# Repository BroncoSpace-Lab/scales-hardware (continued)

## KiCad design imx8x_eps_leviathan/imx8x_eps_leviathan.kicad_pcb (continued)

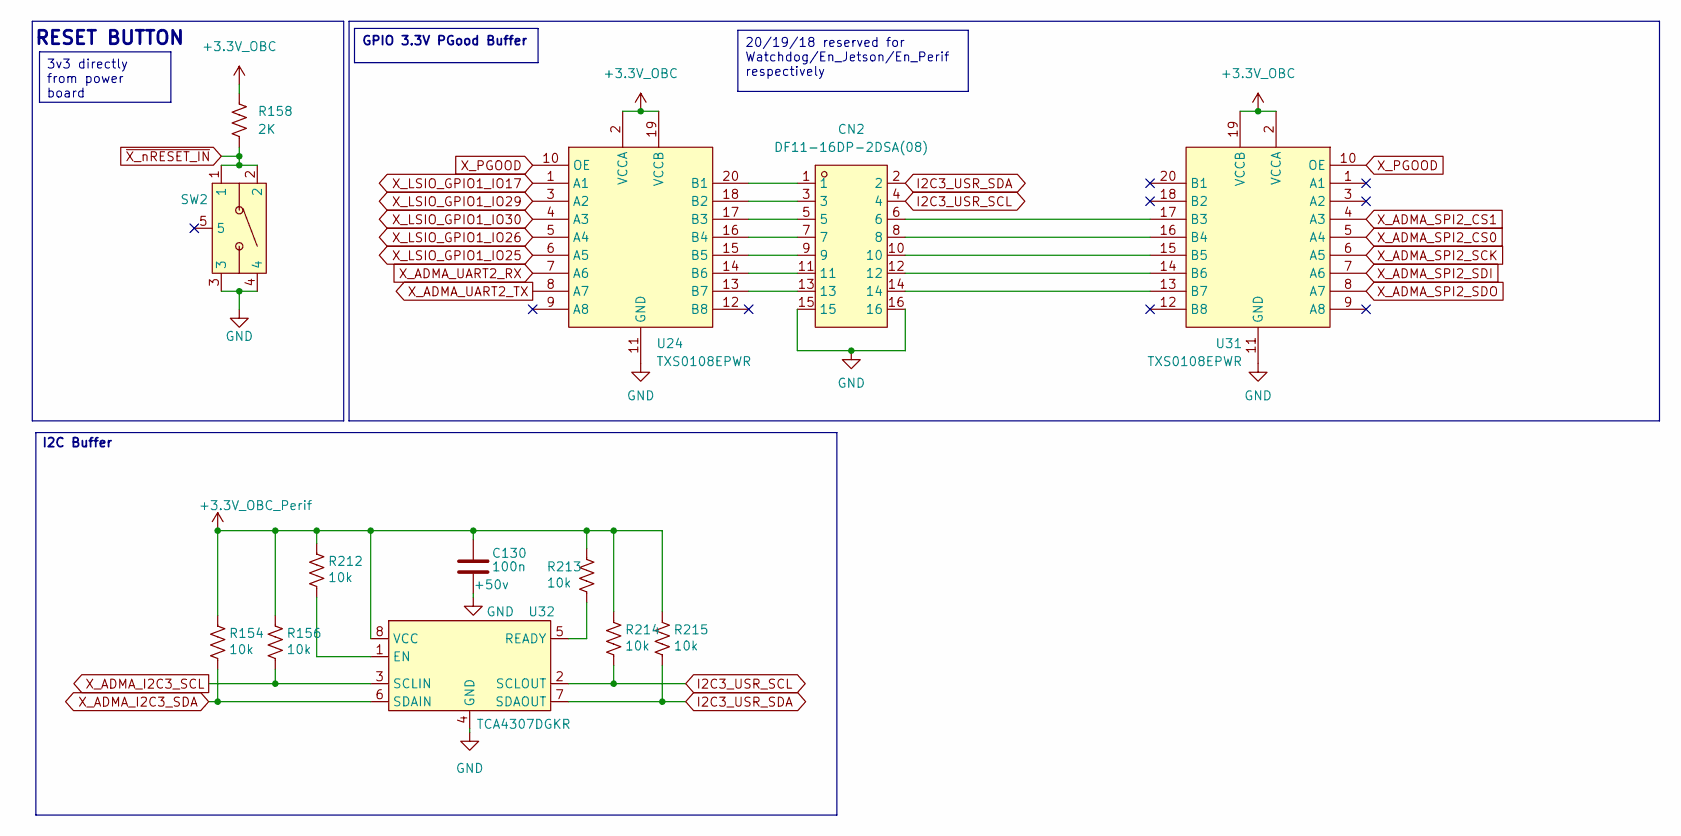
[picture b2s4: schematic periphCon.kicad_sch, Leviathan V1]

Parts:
C130: 100n; C0402; Voltage Rating +50v; LCSC C85858
CN2: DF11-16DP-2DSA(08); CONN-TH_DF11-16DP-2DSA-08; LCSC Part C530981
R154, R156, R212, R213, R214, R215: 10k; R_0603_1608Metric; LCSC C99782
R158: 2K; R0402
SW2: KMR221GLFS; KEY-SMD_KMR2XXGXXX; LCSC Part C72443
U24, U31: TXS0108EPWR; TSSOP-20_L6.5-W4.4-P0.65-LS6.4-BL; LCSC Part C17206
U32: TCA4307DGKR; VSSOP-8_L3.0-W3.0-P0.65-LS4.9-BL; LCSC Part C880333

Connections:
+3.3V_OBC: R158.1, U24.2 (VCCA), U24.19 (VCCB), U31.2 (VCCA), U31.19 (VCCB); also elsewhere on the board
+3.3V_OBC_Perif: C130.1, R154.1, R156.1, R212.1, R213.1, R214.1, R215.1, U32.8 (VCC); also elsewhere on the board
GND: C130.2, CN2.15, CN2.16, SW2.3, SW2.4, U24.11 (GND), U31.11 (GND), U32.4 (GND); also elsewhere on the board
I2C3_USR_SCL: CN2.4, R214.2, U32.2 (SCLOUT)
I2C3_USR_SDA: CN2.2, R215.2, U32.7 (SDAOUT)
unnamed: CN2.1, U24.20 (B1)
unnamed: CN2.3, U24.18 (B2)
unnamed: CN2.5, U24.17 (B3)
unnamed: CN2.7, U24.16 (B4)
unnamed: CN2.9, U24.15 (B5)
unnamed: CN2.11, U24.14 (B6)
unnamed: CN2.13, U24.13 (B7)
unnamed: CN2.6, U31.17 (B3)
unnamed: CN2.8, U31.16 (B4)
unnamed: CN2.10, U31.15 (B5)
unnamed: CN2.12, U31.14 (B6)
unnamed: CN2.14, U31.13 (B7)
unnamed: R212.2, U32.1 (EN)
unnamed: R213.2, U32.5 (READY)
X_ADMA_I2C3_SCL: R156.2, U32.3 (SCLIN); also elsewhere on the board
X_ADMA_I2C3_SDA: R154.2, U32.6 (SDAIN); also elsewhere on the board
X_ADMA_SPI2_CS0: U31.5 (A4); also elsewhere on the board
X_ADMA_SPI2_CS1: U31.4 (A3); also elsewhere on the board
X_ADMA_SPI2_SCK: U31.6 (A5); also elsewhere on the board
X_ADMA_SPI2_SDI: U31.7 (A6); also elsewhere on the board
X_ADMA_SPI2_SDO: U31.8 (A7); also elsewhere on the board
X_ADMA_UART2_RX: U24.7 (A6); also elsewhere on the board
X_ADMA_UART2_TX: U24.8 (A7); also elsewhere on the board
X_LSIO_GPIO1_IO17: U24.1 (A1); also elsewhere on the board
X_LSIO_GPIO1_IO25: U24.6 (A5); also elsewhere on the board
X_LSIO_GPIO1_IO26: U24.5 (A4); also elsewhere on the board
X_LSIO_GPIO1_IO29: U24.3 (A2); also elsewhere on the board
X_LSIO_GPIO1_IO30: U24.4 (A3); also elsewhere on the board
X_PGOOD: U24.10 (OE), U31.10 (OE); also elsewhere on the board
~X_nRESET_IN: R158.2, SW2.1, SW2.2; also elsewhere on the board

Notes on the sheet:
I2C Buffer
RESET BUTTON
20/19/18 reserved for Watchdog/En_Jetson/En_Perif respectively
3v3 directly from power board
GPIO 3.3V PGood Buffer

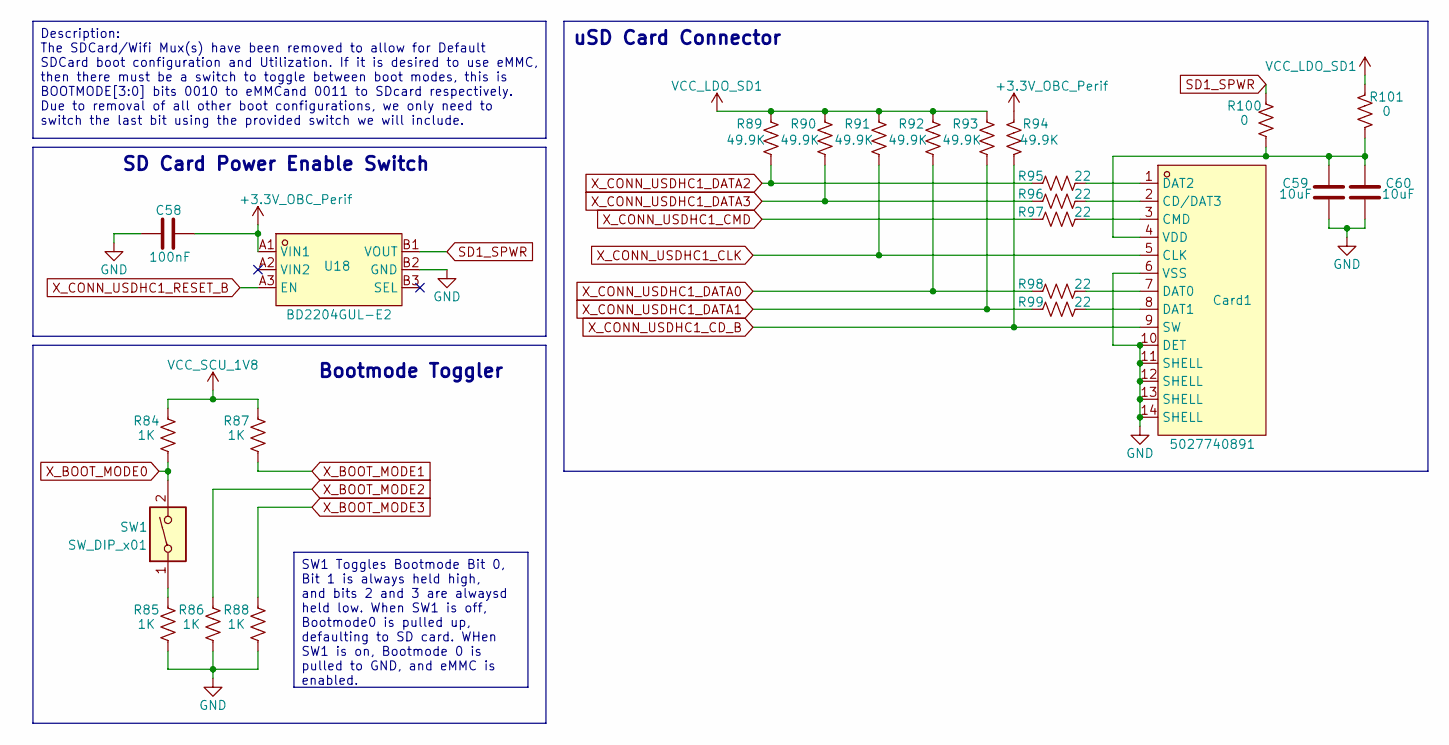
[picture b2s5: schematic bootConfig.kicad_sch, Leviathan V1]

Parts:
C58: 100nF; C0402
C59, C60: 10uF; C0402
Card1: 5027740891; TF-SMD_5027740891; LCSC Part C330255
R84, R85, R86, R87, R88: 1K; R0402
R89, R90, R91, R92, R93, R94: 49.9K; R0402
R95, R96, R97, R98, R99: 22; R0402
R100, R101: 0; R0402
SW1: SW_DIP_x01; SW-SMD_1.27-1P-TPPT
U18: BD2204GUL-E2; BGA-6_L1.5-W1.0-P0.50_BD2204GUL-E2; LCSC Part C314699

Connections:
+3.3V_OBC_Perif: C58.2, R94.2, U18.A1 (VIN1); also elsewhere on the board
GND: C58.1, C59.1, C60.1, Card1.6 (VSS), Card1.10 (DET), Card1.11 (SHELL), Card1.12 (SHELL), Card1.13 (SHELL), Card1.14 (SHELL), R85.1, R86.1, R88.1, U18.B2 (GND); also elsewhere on the board
unnamed: Card1.2 (CD/DAT3), R96.1
unnamed: Card1.3 (CMD), R97.1
unnamed: Card1.7 (DAT0), R98.1
unnamed: Card1.8 (DAT1), R99.1
unnamed: Card1.1 (DAT2), R95.1
unnamed: C59.2, C60.2, Card1.4 (VDD), R100.1, R101.1
unnamed: R85.2, SW1.1
SD1_SPWR: R100.2, U18.B1 (VOUT)
VCC_LDO_SD1: R89.2, R90.2, R91.2, R92.2, R93.2, R101.2; also elsewhere on the board
VCC_SCU_1V8: R84.2, R87.2; also elsewhere on the board
X_BOOT_MODE0: R84.1, SW1.2; also elsewhere on the board
X_BOOT_MODE1: R87.1; also elsewhere on the board
X_BOOT_MODE2: R86.2; also elsewhere on the board
X_BOOT_MODE3: R88.2; also elsewhere on the board
X_CONN_USDHC1_CD_B: Card1.9 (SW), R94.1; also elsewhere on the board
X_CONN_USDHC1_CLK: Card1.5 (CLK), R91.1; also elsewhere on the board
X_CONN_USDHC1_CMD: R97.2; also elsewhere on the board
X_CONN_USDHC1_DATA0: R92.1, R98.2; also elsewhere on the board
X_CONN_USDHC1_DATA1: R93.1, R99.2; also elsewhere on the board
X_CONN_USDHC1_DATA2: R89.1, R95.2; also elsewhere on the board
X_CONN_USDHC1_DATA3: R90.1, R96.2; also elsewhere on the board
X_CONN_USDHC1_RESET_B: U18.A3 (EN); also elsewhere on the board

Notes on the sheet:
uSD Card Connector
SD Card Power Enable Switch
Bootmode Toggler
Description: The SDCard/Wifi Mux(s) have been removed to allow for Default SDCard boot configuration and Utilization. If it is desired to use eMMC, then there must be a switch to toggle between boot modes, this is BOOTMODE[3:0] bits 0010 to eMMCand 0011 to SDcard respectively. Due to removal of all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
SW1 Toggles Bootmode Bit 0, Bit 1 is always held high, and bits 2 and 3 are alwaysd held low. When SW1 is off, Bootmode0 is pulled up, defaulting to SD card. WHen SW1 is on, Bootmode 0 is pulled to GND, and eMMC is enabled.

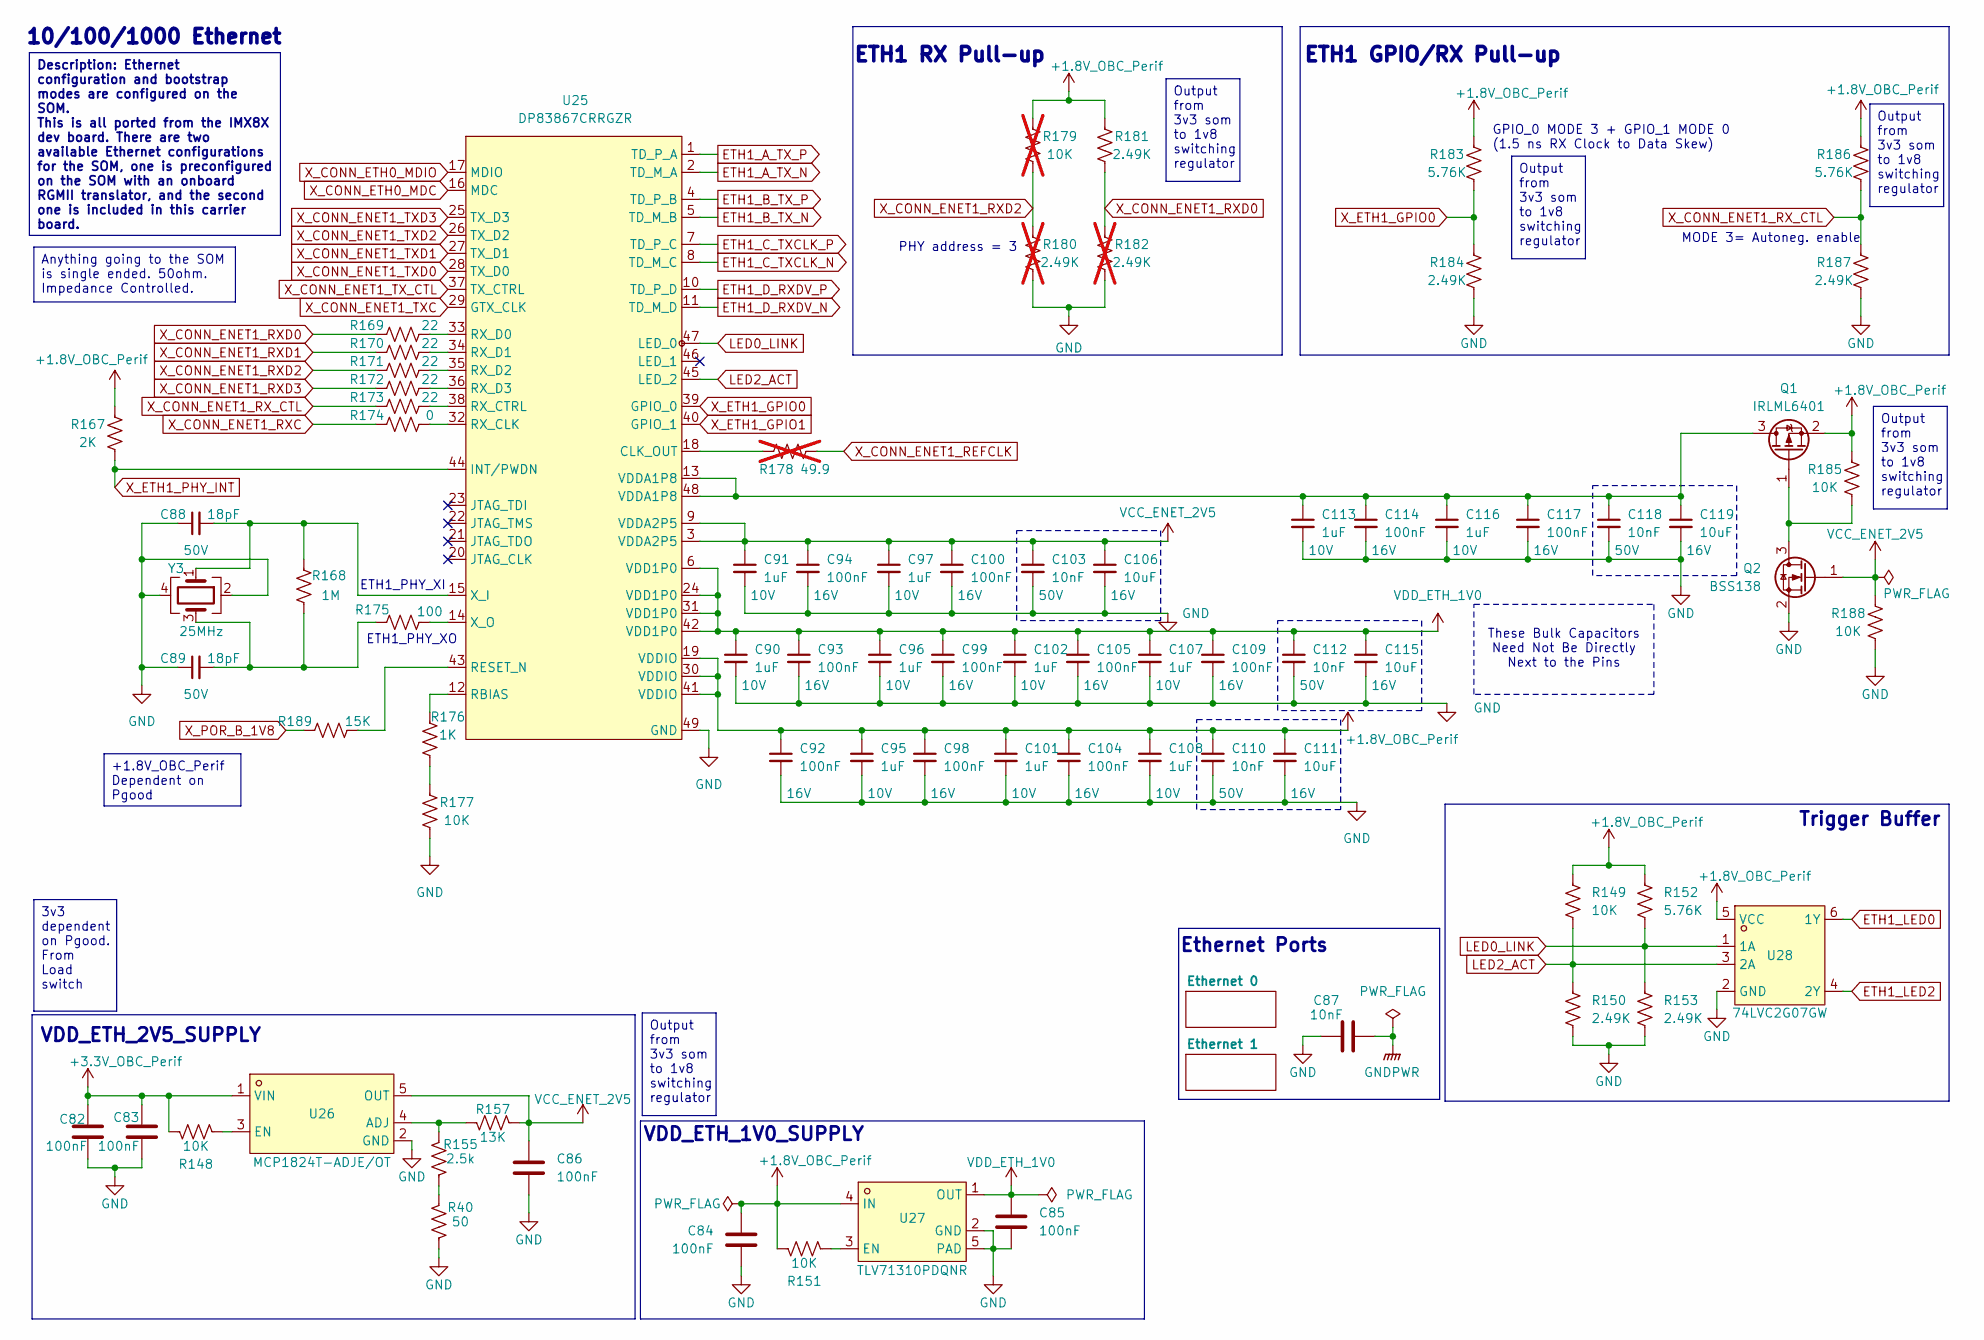
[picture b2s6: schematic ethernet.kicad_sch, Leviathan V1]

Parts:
C82, C83, C84, C85, C86: 100nF; C0402
C87: 10nF; C0402
C88, C89: 18pF; C_0603_1608Metric; Voltage 50V
C90, C91, C95, C96, C97, C101, C102, C107, C108, C113, C116: 1uF; C_0603_1608Metric; Voltage 10V
C92, C93, C94, C98, C99, C100, C104, C105, C109, C114, C117: 100nF; C_0603_1608Metric; Voltage 16V
C103, C110, C112, C118: 10nF; C_0603_1608Metric; Voltage 50V
C106, C111, C115, C119: 10uF; C_0603_1608Metric; Voltage 16V
Q1: IRLML6401; SOT-23
Q2: BSS138; SOT-23
R40: 50; R0402
R148, R149, R151: 10K; R0402
R150, R153: 2.49K; R0402
R152: 5.76K; R0402
R155: 2.5k; R0402
R157: 13K; R0402
R167: 2K; R_0402_1005Metric
R168: 1M; R_0402_1005Metric
R169, R170, R171, R172, R173: 22; R_0402_1005Metric
R174: 0; R_0402_1005Metric
R175: 100; R_0402_1005Metric
R176: 1K; R_0402_1005Metric
R177, R185, R188: 10K; R_0402_1005Metric
R178: 49.9; R_0402_1005Metric; not fitted
R179: 10K; R_0402_1005Metric; not fitted
R180, R182: 2.49K; R_0402_1005Metric; not fitted
R181, R184, R187: 2.49K; R_0402_1005Metric
R183, R186: 5.76K; R_0402_1005Metric
R189: 15K; R_0402_1005Metric
U25: DP83867CRRGZR; VQFN-48_L7.0-W7.0-P0.50-BL-EP4.1; LCSC Part C544766
U26: MCP1824T-ADJE/OT; SOT-23-5_L3.0-W1.7-P0.95-LS2.8-BL; LCSC Part C145717
U27: TLV71310PDQNR; X2SON-4_L1.0-W1.0-P0.65-TL-EP; LCSC Part C2872754
U28: 74LVC2G07GW; SOT-363_L2.1-W1.3-P0.65-LS2.2-BL; LCSC Part C19829574
Y3: 25MHz; CRYSTAL-SMD_4P-L3.2-W2.5-BL-2; LCSC C13740

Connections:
+1.8V_OBC_Perif: C84.1, C92.1, C95.1, C98.1, C101.1, C104.1, C108.1, C110.1, C111.1, Q1.2 (S), R149.1, R151.1, R152.1, R167.2, R179.1, R181.1, R183.1, R185.1, R186.1, U25.19 (VDDIO), U25.30 (VDDIO), U25.41 (VDDIO), U27.4 (IN), U28.5 (VCC); also elsewhere on the board
+3.3V_OBC_Perif: C82.1, C83.1, R148.1, U26.1 (VIN); also elsewhere on the board
ETH1_A_TX_N: U25.2 (TD_M_A); also elsewhere on the board
ETH1_A_TX_P: U25.1 (TD_P_A); also elsewhere on the board
ETH1_B_TX_N: U25.5 (TD_M_B); also elsewhere on the board
ETH1_B_TX_P: U25.4 (TD_P_B); also elsewhere on the board
ETH1_C_TXCLK_N: U25.8 (TD_M_C); also elsewhere on the board
ETH1_C_TXCLK_P: U25.7 (TD_P_C); also elsewhere on the board
ETH1_D_RXDV_N: U25.11 (TD_M_D); also elsewhere on the board
ETH1_D_RXDV_P: U25.10 (TD_P_D); also elsewhere on the board
ETH1_LED0: U28.6 (1Y); also elsewhere on the board
ETH1_LED2: U28.4 (2Y); also elsewhere on the board
GND: C82.2, C83.2, C84.2, C85.2, C86.2, C87.2, C88.1, C89.1, C90.2, C91.2, C92.2, C93.2, C94.2, C95.2, C96.2, C97.2, C98.2, C99.2, C100.2, C101.2, C102.2, C103.2, C104.2, C105.2, C106.2, C107.2, C108.2, C109.2, C110.2, C111.2, C112.2, C113.2, C114.2, C115.2, C116.2, C117.2, C118.2, C119.2, Q2.2 (S), R40.1, R150.2, R153.2, R177.2, R180.2, R182.2, R184.2, R187.2, R188.2, U25.49 (GND), U26.2 (GND), U27.2 (GND), U27.5 (PAD), U28.2 (GND), Y3.2, Y3.4; also elsewhere on the board
GNDPWR: C87.1; also elsewhere on the board
LED0_LINK: R152.2, R153.1, U25.47 (LED_0), U28.1 (1A)
LED2_ACT: R149.2, R150.1, U25.45 (LED_2), U28.3 (2A)
unnamed: C89.2, R168.2, R175.1, Y3.3
unnamed: C113.1, C114.1, C116.1, C117.1, C118.1, C119.1, Q1.3 (D), U25.13 (VDDA1P8), U25.48 (VDDA1P8)
unnamed: Q1.1 (G), Q2.3 (D), R185.2
unnamed: R40.2, R155.1
unnamed: R176.2, R177.1
unnamed: R178.2, U25.18 (CLK_OUT)
unnamed: R176.1, U25.12 (RBIAS)
unnamed: R189.1, U25.43 (RESET_N)
unnamed: R174.1, U25.32 (RX_CLK)
unnamed: R173.1, U25.38 (RX_CTRL)
unnamed: R169.1, U25.33 (RX_D0)
unnamed: R170.1, U25.34 (RX_D1)
unnamed: R171.1, U25.35 (RX_D2)
unnamed: R172.1, U25.36 (RX_D3)
unnamed: C88.2, R168.1, U25.15 (X_I), Y3.1
unnamed: R175.2, U25.14 (X_O)
unnamed: R155.2, R157.1, U26.4 (ADJ)
unnamed: R148.2, U26.3 (EN)
unnamed: R151.2, U27.3 (EN)
VCC_ENET_2V5: C86.1, C91.1, C94.1, C97.1, C100.1, C103.1, C106.1, Q2.1 (G), R157.2, R188.1, U25.3 (VDDA2P5), U25.9 (VDDA2P5), U26.5 (OUT)
VDD_ETH_1V0: C85.1, C90.1, C93.1, C96.1, C99.1, C102.1, C105.1, C107.1, C109.1, C112.1, C115.1, U25.6 (VDD1P0), U25.24 (VDD1P0), U25.31 (VDD1P0), U25.42 (VDD1P0), U27.1 (OUT)
X_CONN_ENET1_REFCLK: R178.1; also elsewhere on the board
X_CONN_ENET1_RXC: R174.2; also elsewhere on the board
X_CONN_ENET1_RXD0: R169.2, R181.2, R182.1; also elsewhere on the board
X_CONN_ENET1_RXD1: R170.2; also elsewhere on the board
X_CONN_ENET1_RXD2: R171.2, R179.2, R180.1; also elsewhere on the board
X_CONN_ENET1_RXD3: R172.2; also elsewhere on the board
X_CONN_ENET1_RX_CTL: R173.2, R186.2, R187.1; also elsewhere on the board
X_CONN_ENET1_TXC: U25.29 (GTX_CLK); also elsewhere on the board
X_CONN_ENET1_TXD0: U25.28 (TX_D0); also elsewhere on the board
X_CONN_ENET1_TXD1: U25.27 (TX_D1); also elsewhere on the board
X_CONN_ENET1_TXD2: U25.26 (TX_D2); also elsewhere on the board
X_CONN_ENET1_TXD3: U25.25 (TX_D3); also elsewhere on the board
X_CONN_ENET1_TX_CTL: U25.37 (TX_CTRL); also elsewhere on the board
X_CONN_ETH0_MDC: U25.16 (MDC); also elsewhere on the board
X_CONN_ETH0_MDIO: U25.17 (MDIO); also elsewhere on the board
X_ETH1_GPIO0: R183.2, R184.1, U25.39 (GPIO_0); also elsewhere on the board
X_ETH1_GPIO1: U25.40 (GPIO_1); also elsewhere on the board
X_ETH1_PHY_INT: R167.1, U25.44 (INT/PWDN); also elsewhere on the board
X_POR_B_1V8: R189.2; also elsewhere on the board

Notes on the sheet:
VDD_ETH_2V5_SUPPLY
Trigger Buffer
GPIO_0 MODE 3 + GPIO_1 MODE 0 (1.5 ns RX Clock to Data Skew)
Ethernet Ports
ETH1 GPIO/RX Pull-up
ETH1_PHY_XI
MODE 3= Autoneg. enable
PHY address = 3
VDD_ETH_1V0_SUPPLY
ETH1 RX Pull-up
10/100/1000 Ethernet
These Bulk Capacitors Need Not Be Directly Next to the Pins
ETH1_PHY_XO
Output from 3v3 som to 1v8 switching regulator
Anything going to the SOM is single ended. 50ohm. Impedance Controlled.
+1.8V_OBC_Perif Dependent on Pgood
3v3 dependent on Pgood. From Load switch
Description: Ethernet configuration and bootstrap modes are configured on the SOM. This is all ported from the IMX8X dev board. There are two available Ethernet configurations for the SOM, one is preconfigured on the SOM with an onboard RGMII translator, and the second one is included in this carri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

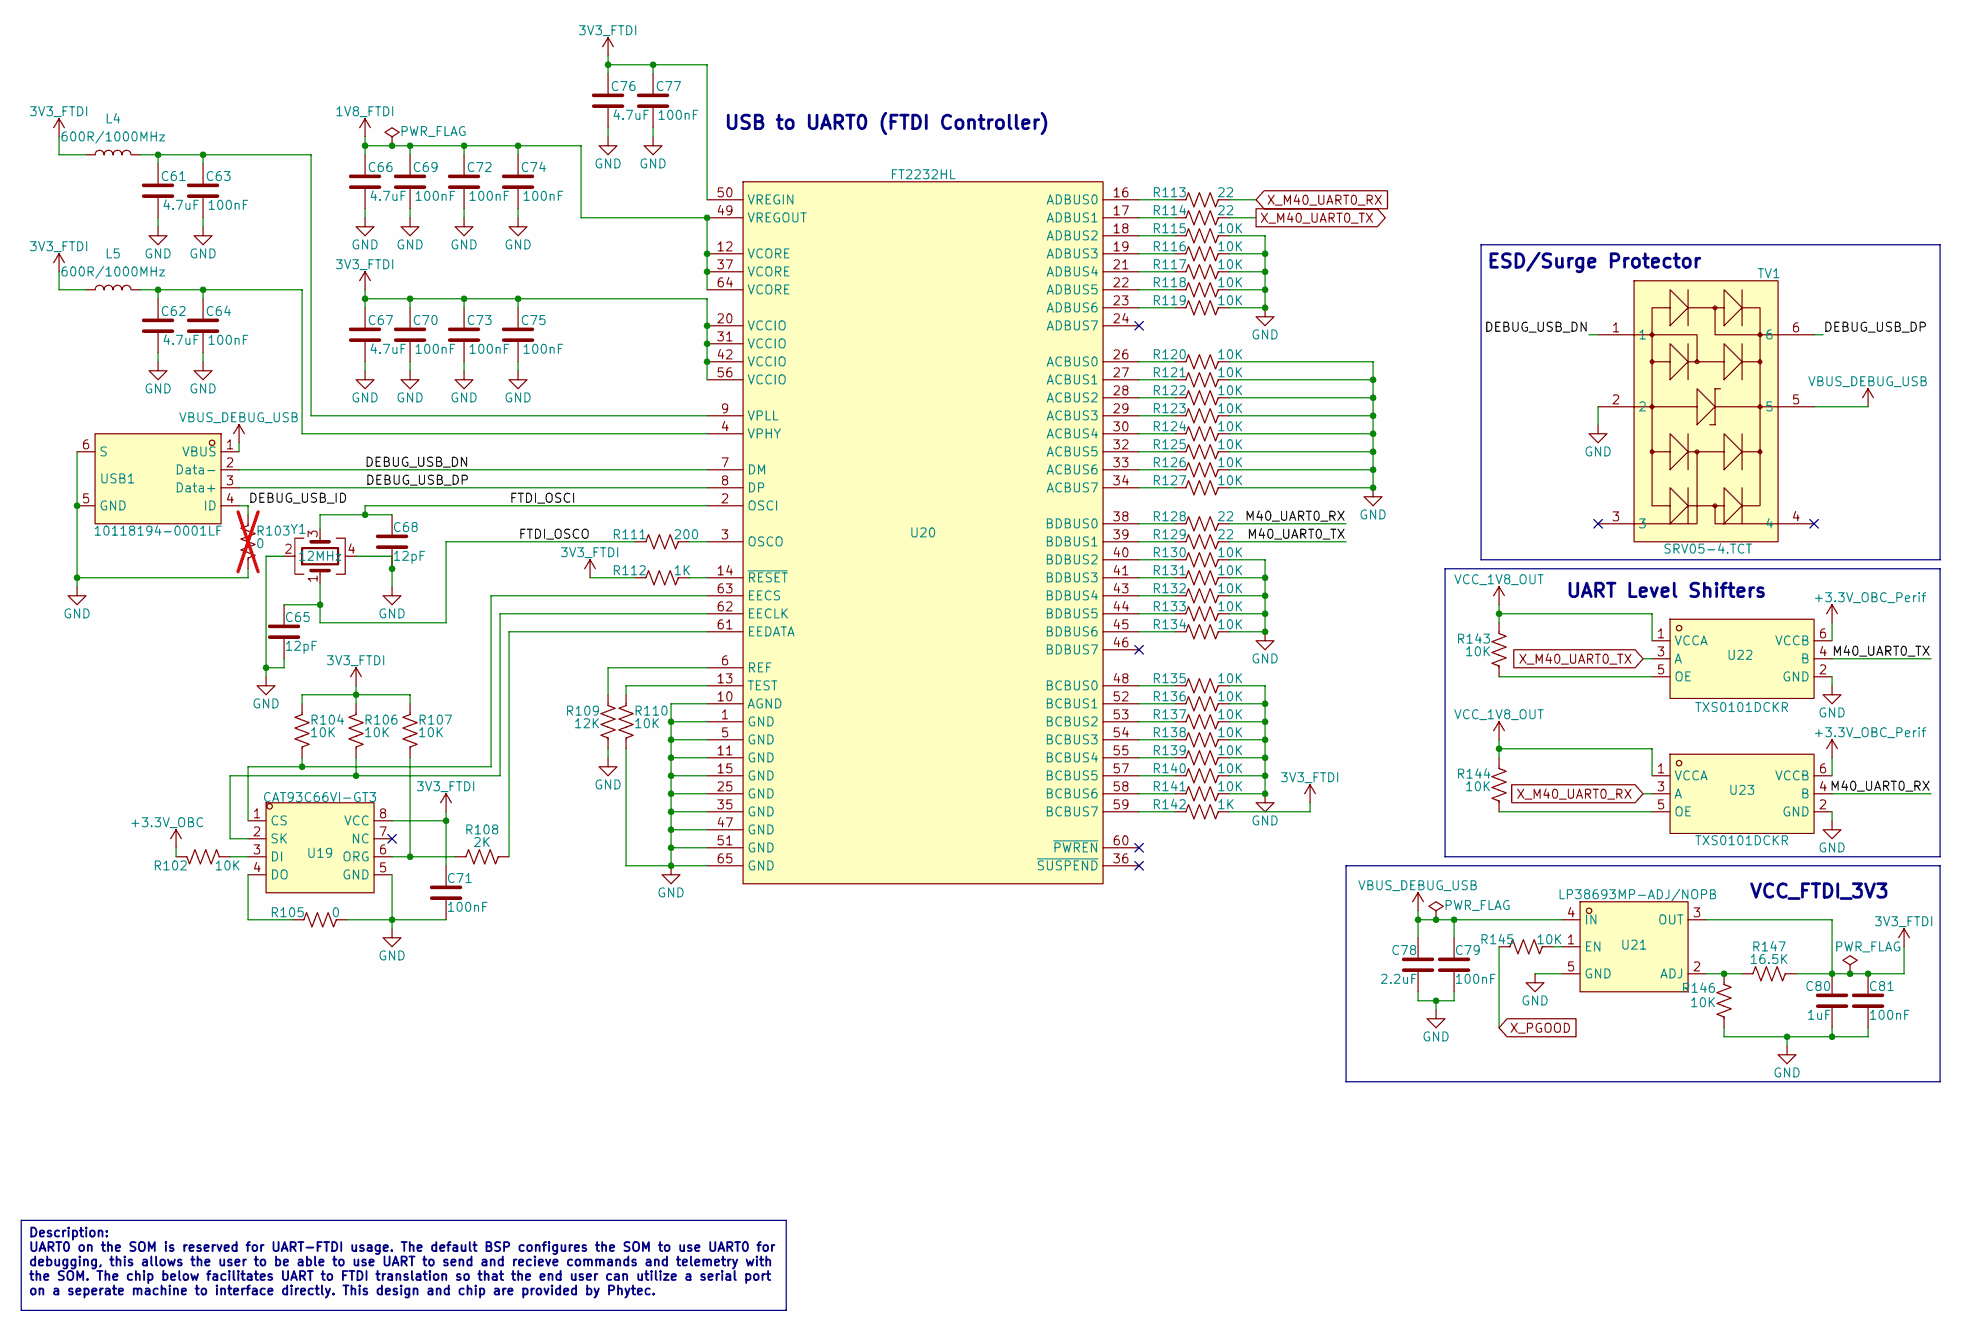
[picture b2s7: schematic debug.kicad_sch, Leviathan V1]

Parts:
C61, C62, C66, C67, C76: 4.7uF; C0402
C63, C64, C69, C70, C71, C72, C73, C74, C75, C77, C79, C81: 100nF; C0402
C65, C68: 12pF; C0402
C78: 2.2uF; C0402
C80: 1uF; C0402
L4, L5: 600R/1000MHz; L0805
R102, R104, R106, R107, R110, R115, R116, R117, R118, R119, R120, R121, R122, R123, R124, R125, R126, R127, R130, R131, R132, R133, R134, R135, R136, R137, R138, R139, R140, R141, R143, R144, R145, R146: 10K; R0402
R103: 0; R0402; not fitted
R105: 0; R0402
R108: 2K; R0402
R109: 12K; R0402
R111: 200; R0402
R112, R142: 1K; R0402
R113, R114, R128, R129: 22; R0402
R147: 16.5K; R0402
TV1: SRV05-4.TCT; SOT-23-6_L2.9-W1.6-P0.95-LS2.8-BR; LCSC Part C13612
U19: CAT93C66VI-GT3; SOIC-8_L4.9-W3.9-P1.27-LS6.0-BL; LCSC Part C890471
U20: FT2232HL; QFN-64_L9.0-W9.0-P0.50-TL-EP4.3; LCSC Part C27882
U21: LP38693MP-ADJ/NOPB; SOT-223-5_L6.5-W3.5-P1.50-LS7.0-BL; LCSC Part C181420
U22, U23: TXS0101DCKR; SC-70-6_L2.0-W1.3-P0.65-LS2.1-BR; LCSC Part C132031
USB1: 10118194-0001LF; MICRO-USB-SMD_10118194-0001LF; LCSC Part C132563
Y1: 12MHz; CRYSTAL-SMD_4P-L3.2-W2.5-BL; LCSC Part C9002

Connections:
1V8_FTDI: C66.2, C69.2, C72.2, C74.2, U20.12 (VCORE), U20.37 (VCORE), U20.49 (VREGOUT), U20.64 (VCORE)
3V3_FTDI: C67.2, C70.2, C71.2, C73.2, C75.2, C76.2, C77.2, C80.2, C81.2, L4.1, L5.1, R104.2, R106.2, R107.2, R112.2, R142.1, R147.1, U19.8 (VCC), U20.20 (VCCIO), U20.31 (VCCIO), U20.42 (VCCIO), U20.50 (VREGIN), U20.56 (VCCIO), U21.3 (OUT)
+3.3V_OBC: R102.2; also elsewhere on the board
+3.3V_OBC_Perif: U22.6 (VCCB), U23.6 (VCCB); also elsewhere on the board
/IMX8XQXP SCALES Mariner Carrier Board/Debug USB - UART/DEBUG_USB_DN: TV1.1, U20.7 (DM), USB1.2 (Data-)
/IMX8XQXP SCALES Mariner Carrier Board/Debug USB - UART/DEBUG_USB_DP: TV1.6, U20.8 (DP), USB1.3 (Data+)
/IMX8XQXP SCALES Mariner Carrier Board/Debug USB - UART/DEBUG_USB_ID: R103.2, USB1.4 (ID)
/IMX8XQXP SCALES Mariner Carrier Board/Debug USB - UART/FTDI_OSCI: C68.2, U20.2 (OSCI), Y1.3
/IMX8XQXP SCALES Mariner Carrier Board/Debug USB - UART/FTDI_OSCO: C65.2, R111.2, Y1.1
/IMX8XQXP SCALES Mariner Carrier Board/Debug USB - UART/M40_UART0_RX: R128.1, U23.4 (B)
/IMX8XQXP SCALES Mariner Carrier Board/Debug USB - UART/M40_UART0_TX: R129.1, U22.4 (B)
GND: C61.1, C62.1, C63.1, C64.1, C65.1, C66.1, C67.1, C68.1, C69.1, C70.1, C71.1, C72.1, C73.1, C74.1, C75.1, C76.1, C77.1, C78.1, C79.1, C80.1, C81.1, R103.1, R105.1, R109.1, R110.1, R115.1, R116.1, R117.1, R118.1, R119.1, R120.1, R121.1, R122.1, R123.1, R124.1, R125.1, R126.1, R127.1, R130.1, R131.1, R132.1, R133.1, R134.1, R135.1, R136.1, R137.1, R138.1, R139.1, R140.1, R141.1, R146.1, TV1.2, U19.5 (GND), U20.1 (GND), U20.5 (GND), U20.10 (AGND), U20.11 (GND), U20.15 (GND), U20.25 (GND), U20.35 (GND), U20.47 (GND), U20.51 (GND), U20.65 (GND), U21.5 (GND), U22.2 (GND), U23.2 (GND), USB1.5 (GND), USB1.6 (S), Y1.2, Y1.4; also elsewhere on the board
unnamed: R104.1, U19.1 (CS), U20.63 (EECS)
unnamed: R102.1, U19.3 (DI)
unnamed: R105.2, U19.4 (DO)
unnamed: R107.1, R108.2, U19.6 (ORG)
unnamed: R106.1, U19.2 (SK), U20.62 (EECLK)
unnamed: R120.2, U20.26 (ACBUS0)
unnamed: R121.2, U20.27 (ACBUS1)
unnamed: R122.2, U20.28 (ACBUS2)
unnamed: R123.2, U20.29 (ACBUS3)
unnamed: R124.2, U20.30 (ACBUS4)
unnamed: R125.2, U20.32 (ACBUS5)
unnamed: R126.2, U20.33 (ACBUS6)
unnamed: R127.2, U20.34 (ACBUS7)
unnamed: R113.2, U20.16 (ADBUS0)
unnamed: R114.2, U20.17 (ADBUS1)
unnamed: R115.2, U20.18 (ADBUS2)
unnamed: R116.2, U20.19 (ADBUS3)
unnamed: R117.2, U20.21 (ADBUS4)
unnamed: R118.2, U20.22 (ADBUS5)
unnamed: R119.2, U20.23 (ADBUS6)
unnamed: R135.2, U20.48 (BCBUS0)
unnamed: R136.2, U20.52 (BCBUS1)
unnamed: R137.2, U20.53 (BCBUS2)
unnamed: R138.2, U20.54 (BCBUS3)
unnamed: R139.2, U20.55 (BCBUS4)
unnamed: R140.2, U20.57 (BCBUS5)
unnamed: R141.2, U20.58 (BCBUS6)
unnamed: R142.2, U20.59 (BCBUS7)
unnamed: R128.2, U20.38 (BDBUS0)
unnamed: R129.2, U20.39 (BDBUS1)
unnamed: R130.2, U20.40 (BDBUS2)
unnamed: R131.2, U20.41 (BDBUS3)
unnamed: R132.2, U20.43 (BDBUS4)
unnamed: R133.2, U20.44 (BDBUS5)
unnamed: R134.2, U20.45 (BDBUS6)
unnamed: R108.1, U20.61 (EEDATA)
unnamed: R111.1, U20.3 (OSCO)
unnamed: R109.2, U20.6 (REF)
unnamed: R110.2, U20.13 (TEST)
unnamed: C62.2, C64.2, L5.2, U20.4 (VPHY)
unnamed: C61.2, C63.2, L4.2, U20.9 (VPLL)
unnamed: R112.1, U20.14 (~RESET)
unnamed: R146.2, R147.2, U21.2 (ADJ)
unnamed: R145.1, U21.1 (EN)
unnamed: R143.1, U22.5 (OE)
unnamed: R144.1, U23.5 (OE)
VBUS_DEBUG_USB: C78.2, C79.2, TV1.5, U21.4 (IN), USB1.1 (VBUS)
VCC_1V8_OUT: R143.2, R144.2, U22.1 (VCCA), U23.1 (VCCA); also elsewhere on the board
X_M40_UART0_RX: R113.1, U23.3 (A); also elsewhere on the board
X_M40_UART0_TX: R114.1, U22.3 (A); also elsewhere on the board
X_PGOOD: R145.2; also elsewhere on the board

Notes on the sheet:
UART Level Shifters
VCC_FTDI_3V3
USB to UART0 (FTDI Controller)
ESD/Surge Protector
Description: UART0 on the SOM is reserved for UART-FTDI usage. The default BSP configures the SOM to use UART0 for debugging, this allows the user to be able to use UART to send and recieve commands and telemetry with the SOM. The chip below facilitates UART to FTDI translation so that the end user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

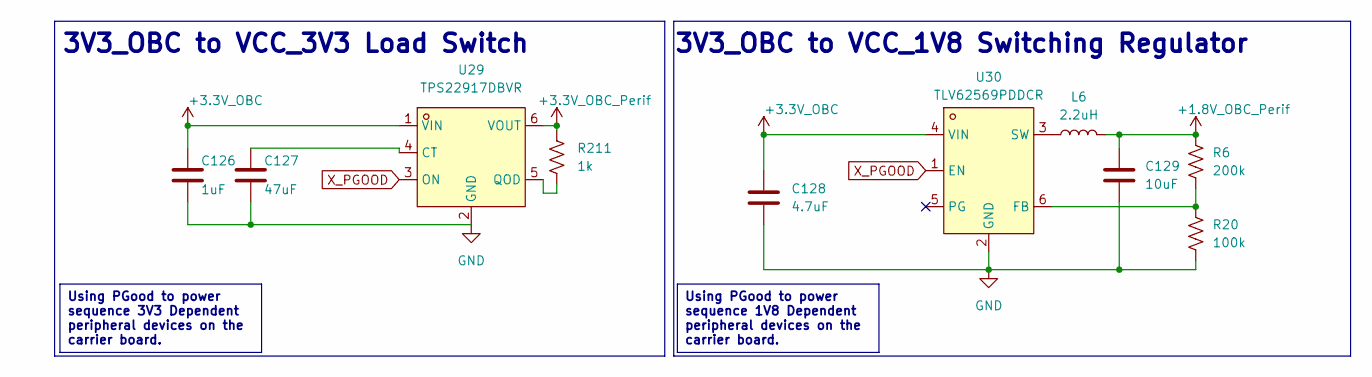
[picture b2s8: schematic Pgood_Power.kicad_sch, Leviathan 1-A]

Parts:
C126: 1uF; C_0603_1608Metric
C127: 47uF; C_0603_1608Metric
C128: 4.7uF; C_0603_1608Metric
C129: 10uF; C_0603_1608Metric
L6: 2.2uH; IND-SMD_L2.5-W2.0_YXMBL252010P; LCSC Part C5349606
R6: 200k; R0402
R20: 100k; R0402
R211: 1k; R0402
U29: TPS22917DBVR; SOT-23-6_L2.9-W1.6-P0.95-LS2.8-BR; LCSC Part C2681320
U30: TLV62569PDDCR; SOT-23-6_L2.9-W1.6-P0.95-LS2.8-BL; LCSC Part C398365

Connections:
+1.8V_OBC_Perif: C129.1, L6.2, R6.1; also elsewhere on the board
+3.3V_OBC: C126.1, C128.1, U29.1 (VIN), U30.4 (VIN); also elsewhere on the board
+3.3V_OBC_Perif: R211.1, U29.6 (VOUT); also elsewhere on the board
GND: C126.2, C127.2, C128.2, C129.2, R20.2, U29.2 (GND), U30.2 (GND); also elsewhere on the board
unnamed: C127.1, U29.4 (CT)
unnamed: R211.2, U29.5 (QOD)
unnamed: R6.2, R20.1, U30.6 (FB)
unnamed: L6.1, U30.3 (SW)
X_PGOOD: U29.3 (ON), U30.1 (EN); also elsewhere on the board

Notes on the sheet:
3V3_OBC to VCC_3V3 Load Switch
3V3_OBC to VCC_1V8 Switching Regulator
Using PGood to power sequence 3V3 Dependent peripheral devices on the carrier board.
Using PGood to power sequence 1V8 Dependent peripheral devices on the carrier board.

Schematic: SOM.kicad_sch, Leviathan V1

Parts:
C120, C121: 22uF; C_0603_1608Metric; Voltage 25V
C122, C123: 4.7uF; C_0603_1608Metric; Voltage 10V
C124: 100nF; C_0603_1608Metric; Voltage 16V
C125: 220nF; C_0603_1608Metric
J9, J10: BTH-070-02-L-D-A; SAMTEC_BTH-070-02-L-D-A; PARTREV R
R190, R191, R192, R193, R194, R195: 22; R_0402_1005Metric
R196, R197, R198, R199, R200, R201, R202, R203, R204, R205, R206, R207, R208, R209, R210: 10k; R_0402_1005Metric
TP16, TP17, TP47, TP49: TestPoint; TestPoint_THTPad_1.0x1.0mm_Drill0.5mm

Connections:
+3.3V_OBC: C120.1, C121.1, C122.1, C123.1, C124.1, J10.132 (D66), J10.133 (C67), J10.134 (D67), J10.135 (C68), J10.136 (D68), J10.137 (C69), J10.138 (D69), J10.139 (C70), J10.140 (D70); also elsewhere on the board
GND: C120.2, C121.2, C122.2, C123.2, C124.2, C125.2, J9.03 (A2), J9.06 (B3), J9.09 (A5), J9.12 (B6), J9.13 (A7), J9.18 (B9), J9.23 (A12), J9.24 (B12), J9.30 (B15), J9.36 (B18), J9.39 (A20), J9.40 (B20), J9.46 (B23), J9.49 (A25), J9.52 (B26), J9.58 (B29), J9.61 (A31), J9.64 (B32), J9.71 (A36), J9.74 (B37), J9.79 (A40), J9.80 (B40), J9.89 (A45), J9.90 (B45), J9.100 (B50), J9.103 (A52), J9.108 (B54), J9.111 (A56), J9.120 (B60), J9.121 (A61), J9.126 (B63), J9.131 (A66), J9.139 (A70), J9.140 (B70), J10.09 (C5), J10.10 (D5), J10.19 (C10), J10.22 (D11), J10.29 (C15), J10.36 (D18), J10.39 (C20), J10.46 (D23), J10.49 (C25), J10.56 (D28), J10.59 (C30), J10.62 (D31), J10.69 (C35), J10.70 (D35), J10.79 (C40), J10.80 (D40), J10.89 (C45), J10.90 (D45), J10.95 (C48), J10.100 (D50), J10.107 (C54), J10.112 (D56), J10.115 (C58), J10.120 (D60), J10.125 (C63), J10.130 (D65), R196.1, R197.1, R198.1, R199.1, R200.1, R201.1, R202.1, R203.1, R204.1, R205.1, R206.1, R207.1, R208.1, R209.1, R210.1; also elsewhere on the board
unnamed: J9.25 (A13), R190.2
unnamed: J9.27 (A14), R191.2
unnamed: J9.29 (A15), R192.2
unnamed: J9.31 (A16), R193.2
unnamed: J9.35 (A18), R194.2
unnamed: J9.37 (A19), R195.2
unnamed: J9.02 (B1), R198.2
unnamed: J9.04 (B2), R199.2
unnamed: J9.08 (B4), R200.2
unnamed: J9.10 (B5), R201.2
unnamed: J9.26 (B13), J9.28 (B14), R196.2
unnamed: J9.32 (B16), J9.34 (B17), R197.2
unnamed: J10.31 (C16), J10.33 (C17), J10.35 (C18), J10.37 (C19), R202.2
unnamed: J10.41 (C21), J10.43 (C22), J10.45 (C23), J10.47 (C24), R203.2
unnamed: J10.51 (C26), J10.53 (C27), J10.55 (C28), J10.57 (C29), R204.2
unnamed: J10.61 (C31), J10.63 (C32), J10.65 (C33), J10.67 (C34), R205.2
unnamed: J10.71 (C36), J10.73 (C37), J10.75 (C38), J10.77 (C39), R206.2
unnamed: J10.64 (D32), R210.2
unnamed: J10.76 (D38), J10.78 (D39), R207.2
unnamed: J10.82 (D41), J10.84 (D42), J10.86 (D43), J10.88 (D44), R208.2
unnamed: J10.92 (D46), J10.94 (D47), J10.96 (D48), J10.98 (D49), R209.2
VCC_1V8_OUT: J10.127 (C64), TP47.1; also elsewhere on the board
VCC_3V3_OUT: J10.129 (C65), TP17.1
VCC_LDO_SD1: J9.33 (A17); also elsewhere on the board
VCC_QSPI_1V8: J10.20 (D10)
VCC_SCU_1V8: J10.93 (C47); also elsewhere on the board
VDD_ADC_1V8: C125.1, J10.114 (D57)
X_ADMA_I2C0_SCL: J10.66 (D33); also elsewhere on the board
X_ADMA_I2C0_SDA: J10.68 (D34); also elsewhere on the board
X_ADMA_I2C3_SCL: J9.112 (B56); also elsewhere on the board
X_ADMA_I2C3_SDA: J9.107 (A54); also elsewhere on the board
X_ADMA_SPI2_CS0: J9.41 (A21); also elsewhere on the board
X_ADMA_SPI2_CS1: J9.67 (A34); also elsewhere on the board
X_ADMA_SPI2_SCK: J9.43 (A22); also elsewhere on the board
X_ADMA_SPI2_SDI: J9.45 (A23); also elsewhere on the board
X_ADMA_SPI2_SDO: J9.47 (A24); also elsewhere on the board
X_ADMA_UART0_RX: J9.97 (A49)
X_ADMA_UART0_TX: J9.95 (A48)
X_ADMA_UART2_RX: J9.99 (A50); also elsewhere on the board
X_ADMA_UART2_TX: J9.101 (A51); also elsewhere on the board
X_BOOT_MODE0: J9.66 (B33); also elsewhere on the board
X_BOOT_MODE1: J9.68 (B34); also elsewhere on the board
X_BOOT_MODE2: J9.70 (B35); also elsewhere on the board
X_BOOT_MODE3: J9.72 (B36); also elsewhere on the board
X_CONN_ENET1_REFCLK: J9.106 (B53); also elsewhere on the board
X_CONN_ENET1_RXC: J9.86 (B43); also elsewhere on the board
X_CONN_ENET1_RXD0: J9.102 (B51); also elsewhere on the board
X_CONN_ENET1_RXD1: J9.94 (B47); also elsewhere on the board
X_CONN_ENET1_RXD2: J9.92 (B46); also elsewhere on the board
X_CONN_ENET1_RXD3: J9.88 (B44); also elsewhere on the board
X_CONN_ENET1_RX_CTL: J9.104 (B52); also elsewhere on the board
X_CONN_ENET1_TXC: J9.78 (B39); also elsewhere on the board
X_CONN_ENET1_TXD0: J9.96 (B48); also elsewhere on the board
X_CONN_ENET1_TXD1: J9.98 (B49); also elsewhere on the board
X_CONN_ENET1_TXD2: J9.76 (B38); also elsewhere on the board
X_CONN_ENET1_TXD3: J9.82 (B41); also elsewhere on the board
X_CONN_ENET1_TX_CTL: J9.84 (B42); also elsewhere on the board
X_CONN_ETH0_MDC: J9.135 (A68); also elsewhere on the board
X_CONN_ETH0_MDIO: J9.133 (A67); also elsewhere on the board
X_CONN_USDHC1_CD_B: J9.19 (A10); also elsewhere on the board
X_CONN_USDHC1_CLK: R194.1; also elsewhere on the board
X_CONN_USDHC1_CMD: R195.1; also elsewhere on the board
X_CONN_USDHC1_DATA0: R193.1; also elsewhere on the board
X_CONN_USDHC1_DATA1: R192.1; also elsewhere on the board
X_CONN_USDHC1_DATA2: R191.1; also elsewhere on the board
X_CONN_USDHC1_DATA3: R190.1; also elsewhere on the board
X_CONN_USDHC1_RESET_B: J9.21 (A11); also elsewhere on the board
X_CONN_USDHC1_VSELECT: J9.15 (A8)
X_ETH0_A_TX_N: J9.136 (B68); also elsewhere on the board
X_ETH0_A_TX_P: J9.138 (B69); also elsewhere on the board
X_ETH0_B_TX_N: J9.132 (B66); also elsewhere on the board
X_ETH0_B_TX_P: J9.134 (B67); also elsewhere on the board
X_ETH0_C_TXCLK_N: J9.128 (B64); also elsewhere on the board
X_ETH0_C_TXCLK_P: J9.130 (B65); also elsewhere on the board
X_ETH0_D_RXDV_N: J9.122 (B61); also elsewhere on the board
X_ETH0_D_RXDV_P: J9.124 (B62); also elsewhere on the board
X_ETH0_GPIO0: J9.127 (A64)
X_ETH0_GPIO1: J9.129 (A65)
X_ETH0_INT: J9.137 (A69), TP16.1
X_ETH0_LED0: J9.123 (A62); also elsewhere on the board
X_ETH0_LED1: J9.125 (A63); also elsewhere on the board
X_ETH1_GPIO0: J10.122 (D61); also elsewhere on the board
X_ETH1_GPIO1: J10.128 (D64); also elsewhere on the board
X_ETH1_PHY_INT: J10.126 (D63); also elsewhere on the board
X_LSIO_GPIO1_IO09: J10.116 (D58)
X_LSIO_GPIO1_IO10: J10.118 (D59)
X_LSIO_GPIO1_IO17: J9.85 (A43); also elsewhere on the board
X_LSIO_GPIO1_IO18: J9.87 (A44); also elsewhere on the board
X_LSIO_GPIO1_IO19: J9.93 (A47); also elsewhere on the board
X_LSIO_GPIO1_IO20: J9.91 (A46); also elsewhere on the board
X_LSIO_GPIO1_IO25: J10.23 (C12); also elsewhere on the board
X_LSIO_GPIO1_IO26: J10.21 (C11); also elsewhere on the board
X_LSIO_GPIO1_IO29: J10.81 (C41); also elsewhere on the board
X_LSIO_GPIO1_IO30: J10.83 (C42); also elsewhere on the board
X_M40_UART0_RX: J10.121 (C61); also elsewhere on the board
X_M40_UART0_TX: J10.123 (C62); also elsewhere on the board
X_PGOOD: J10.105 (C53); also elsewhere on the board
X_PMIC_EWARN: J10.109 (C55)
X_PMIC_INT_B: J10.117 (C59)
X_PMIC_WDI: J10.119 (C60)
X_POR_B_1V8: J10.101 (C51); also elsewhere on the board
X_POR_B_3V3: J10.103 (C52), TP49.1
X_SCU_PMIC_ON_REQ: J10.111 (C56)
X_SCU_PMIC_STANDBY: J10.113 (C57)
~X_nRESET_IN: J10.91 (C46); also elsewhere on the board

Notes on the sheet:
ETH0_GPIO go to pin headers
Switch the watchdog and the m40 uart
X2 Connector: Pins C through D
I2C0_SCL/SDA Reserved for Power Board Diagnostics. I2C3_SCL/SDA is open for end user.
Consider sequencing peripheral power with P_GOOD using a load switch. page 27 of the HW manual to ensure SOM safety
X1 Connector: Pins A through B
